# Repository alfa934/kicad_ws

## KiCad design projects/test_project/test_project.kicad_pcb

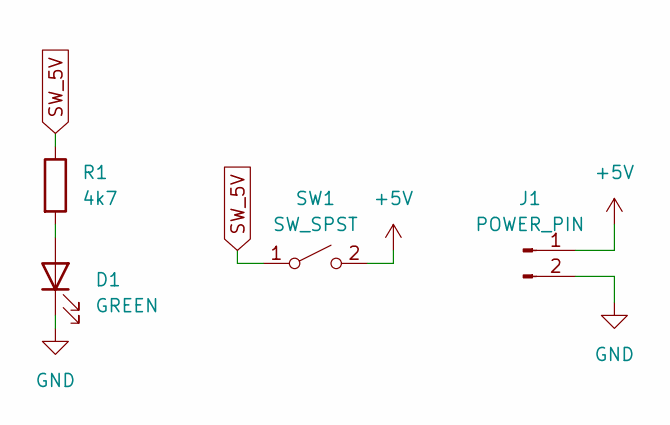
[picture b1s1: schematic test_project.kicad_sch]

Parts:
D1: GREEN; LED_D5.0mm
J1: POWER_PIN; JST_XH_B2B-XH-A_1x02_P2.50mm_Vertical
R1: 4k7; R_Axial_DIN0411_L9.9mm_D3.6mm_P12.70mm_Horizontal
SW1: SW_SPST; SW_DIP_SPSTx01_Slide_9.78x4.72mm_W7.62mm_P2.54mm

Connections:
+5V: J1.1, SW1.2 (B)
GND: D1.1 (K), J1.2
unnamed: D1.2 (A), R1.2
SW_5V: R1.1, SW1.1 (A)

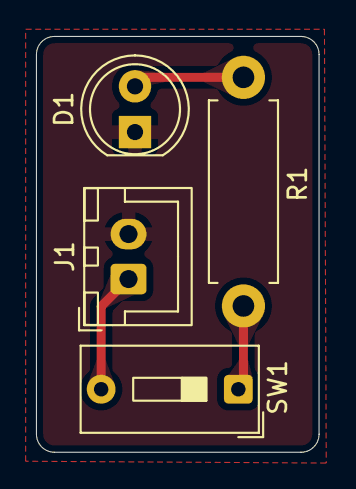
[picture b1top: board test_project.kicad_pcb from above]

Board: 2 copper layers, 15.7 x 23.1 mm, 4 parts (0 on the bottom side), 4 nets.
